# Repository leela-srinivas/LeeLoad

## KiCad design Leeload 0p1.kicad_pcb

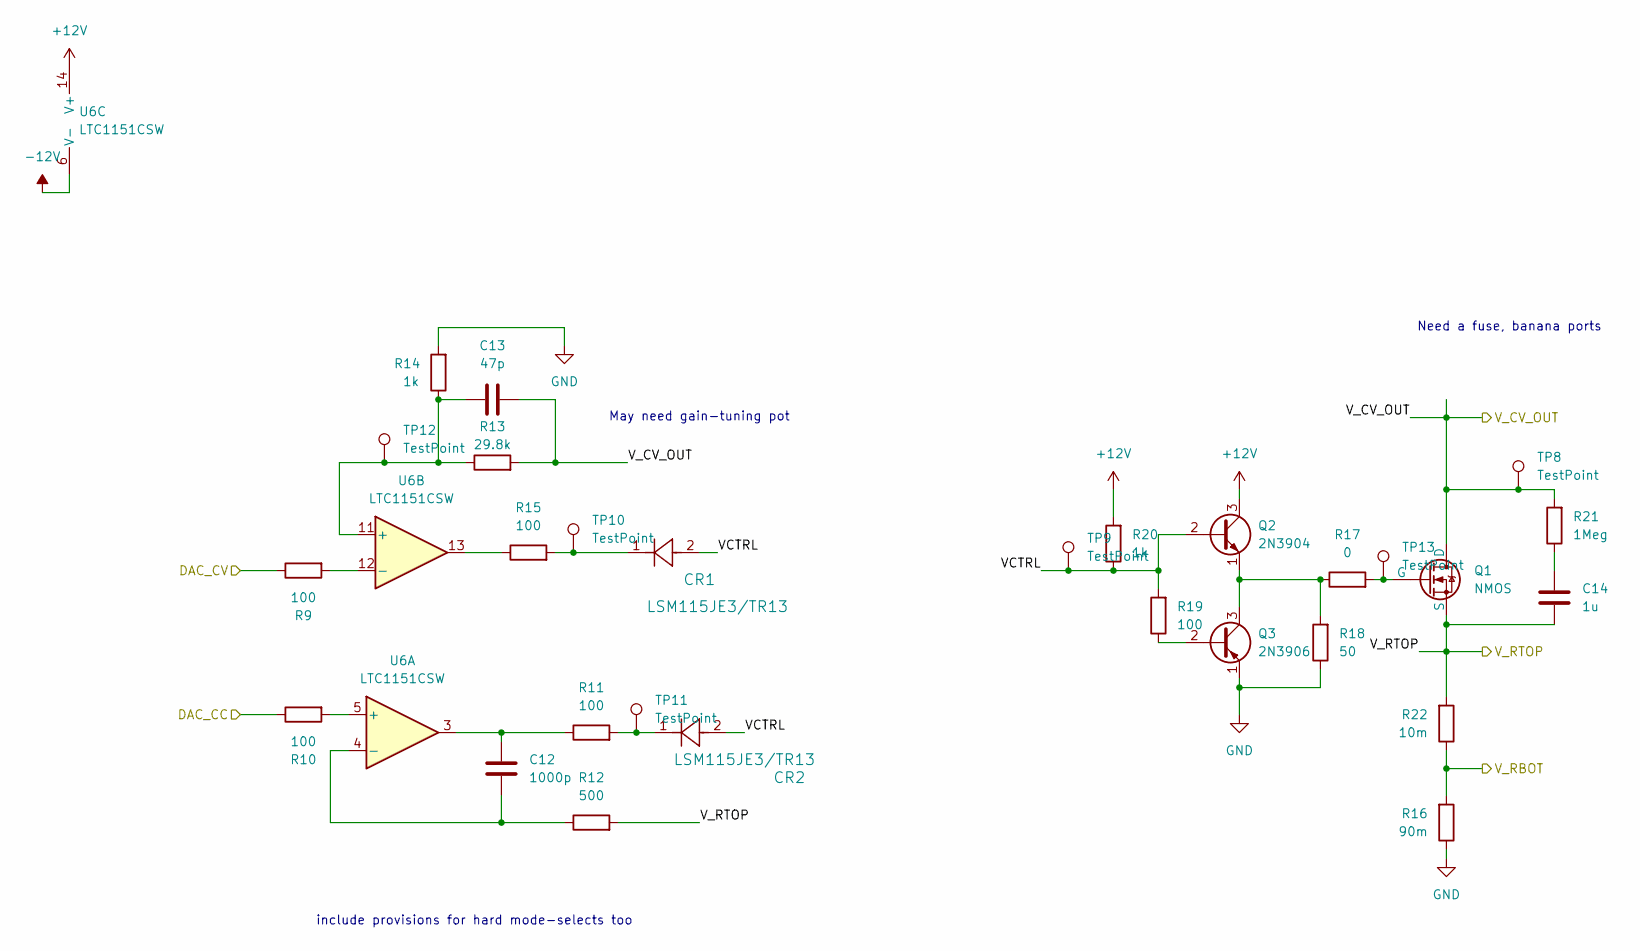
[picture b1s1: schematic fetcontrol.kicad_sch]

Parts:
C12: 1000p
C13: 47p; C_0402_1005Metric
C14: 1u; C_0402_1005Metric
CR1, CR2: LSM115JE3/TR13; DO-214BA_MCH
Q1: NMOS; TO-220-3_Vertical
Q2: 2N3904; TO-92_Inline
Q3: 2N3906; TO-92_Inline
R9, R10, R11, R15, R19: 100; R_0402_1005Metric
R12: 500; R_0402_1005Metric
R13: 29.8k; R_0402_1005Metric
R14, R20: 1k; R_0402_1005Metric
R16: 90m; R_Box_L26.0mm_W5.0mm_P20.00mm
R17: 0; R_0402_1005Metric
R18: 50; R_0402_1005Metric
R21: 1Meg; R_0402_1005Metric
R22: 10m; R_0402_1005Metric
TP8: TestPoint; TestPoint_Plated_Hole_D2.0mm
TP9, TP10, TP11, TP12, TP13: TestPoint; TestPoint_Pad_D1.0mm
U6: LTC1151CSW; SOIC-16W_7.5x10.3mm_P1.27mm

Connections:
12V_REG: Q2.3 (C), R20.2, U6.6 (V-), U6.14 (V+); also elsewhere on the board
/Arduino Control/DAC_CC: R10.1; also elsewhere on the board
/Arduino Control/DAC_CV: R9.1; also elsewhere on the board
/Arduino Control/IN-: R16.2, R22.1; also elsewhere on the board
/Control Loops, FET Control/VCTRL: CR1.2, CR2.2, Q2.2 (B), R19.2, R20.1, TP9.1
/Control Loops, FET Control/V_CV_OUT: C13.2, Q1.1 (D), R13.2, R21.2, TP8.1; also elsewhere on the board
/Control Loops, FET Control/V_RTOP: C14.1, Q1.3 (S), R12.2, R22.2; also elsewhere on the board
GND: Q3.1 (E), R14.2, R16.1, R18.1; also elsewhere on the board
unnamed: C12.1, R11.1, U6.3
unnamed: C14.2, R21.1
unnamed: CR1.1, R15.2, TP10.1
unnamed: CR2.1, R11.2, TP11.1
unnamed: Q1.2 (G), R17.2, TP13.1
unnamed: Q2.1 (E), Q3.3 (C), R17.1, R18.2
unnamed: Q3.2 (B), R19.1
unnamed: R15.1, U6.13
unnamed: R10.2, U6.5 (+)
unnamed: C12.2, R12.1, U6.4 (-)
unnamed: C13.1, R13.1, R14.1, TP12.1, U6.11 (+)
unnamed: R9.2, U6.12 (-)

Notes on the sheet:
include provisions for hard mode-selects too
Need a fuse, banana ports
May need gain-tuning pot

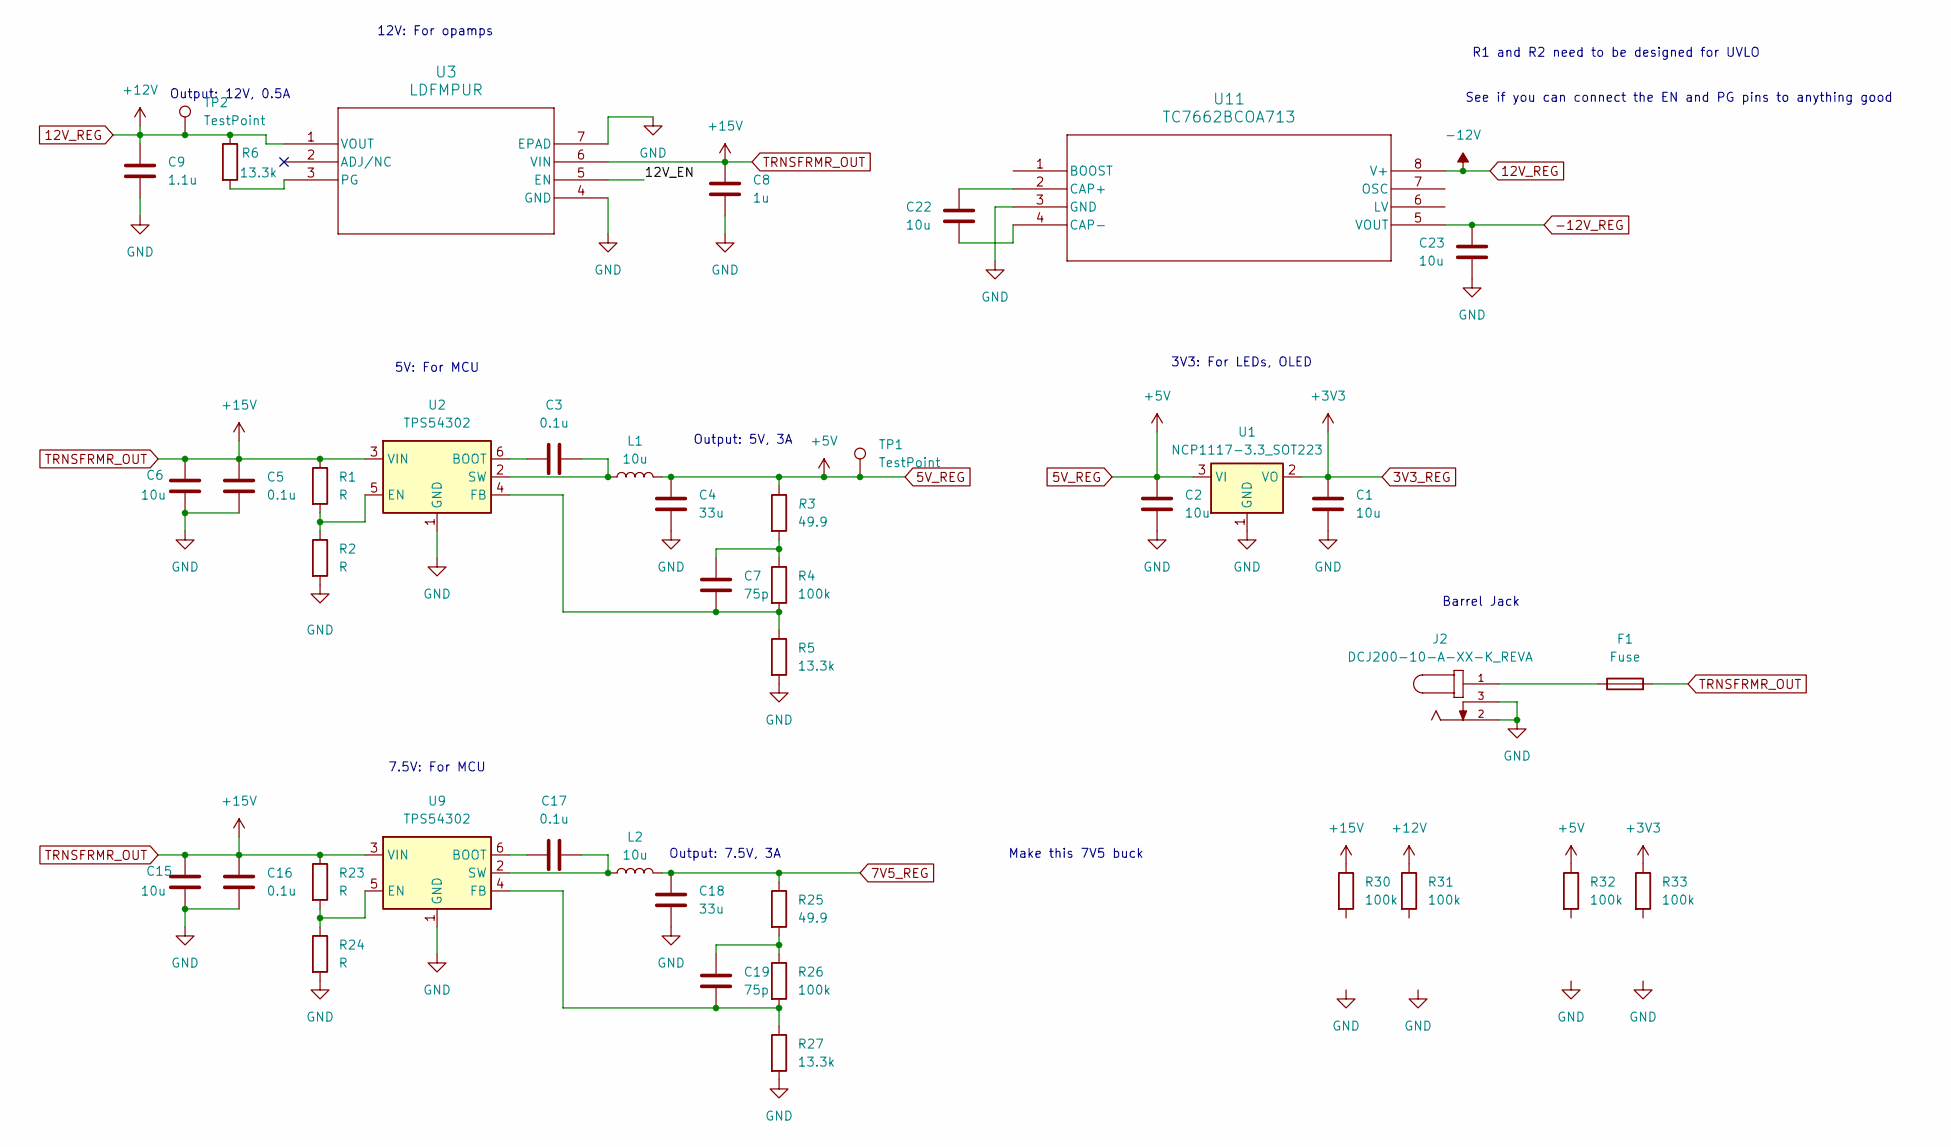
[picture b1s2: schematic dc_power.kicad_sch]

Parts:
C1, C2, C6: 10u; C_0603_1608Metric
C3: 0.1u; C_0805_2012Metric_Pad1.18x1.45mm_HandSolder
C4: 33u; C_0402_1005Metric
C5, C16, C17: 0.1u; C_0402_1005Metric
C7, C19: 75p; C_0402_1005Metric
C8: 1u; CP_Radial_D4.0mm_P2.00mm
C9: 1.1u; C_0805_2012Metric
C15: 10u; C_0402_1005Metric
C18: 33u; C_0805_2012Metric
C22, C23: 10u; CP_Radial_D5.0mm_P2.50mm
F1: Fuse
J2: DCJ200-10-A-XX-K_REVA; GCT_DCJ200-10-A-XX-K_REVA; PARTREV A
L1, L2: 10u; L_1206_3216Metric_Pad1.22x1.90mm_HandSolder
R1, R2: R; R_0402_1005Metric
R3: 49.9; R_0603_1608Metric
R4, R26: 100k; R_0603_1608Metric
R5, R27: 13.3k; R_0603_1608Metric
R6: 13.3k
R23, R24: R
R25: 49.9; C_0402_1005Metric
R30, R31, R32, R33: 100k
TP1, TP2: TestPoint; TestPoint_Plated_Hole_D2.0mm
U1: NCP1117-3.3_SOT223; SOT-223-3_TabPin2
U2, U9: TPS54302; SOT-23-6
U3: LDFMPUR; DFN6_3x3_LDFM_STM
U11: TC7662BCOA713; SOIC8-N_MC_MCH

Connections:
3V3_REG: C1.1, R33.1, U1.2 (VO); also elsewhere on the board
5V_REG: C2.1, C4.2, L1.2, R3.1, R32.1, TP1.1, U1.3 (VI); also elsewhere on the board
7V5_REG: C18.2, L2.2, R25.1
12V_REG: C9.2, R6.1, R31.1, TP2.1, U3.1 (VOUT), U11.8 (V+); also elsewhere on the board
-12V_REG: C23.1, U11.5 (VOUT)
/DC Power/12V_EN: U3.5 (EN)
GND: C1.2, C2.2, C4.1, C5.1, C6.2, C8.1, C9.1, C15.2, C16.1, C18.1, C23.2, J2.2, J2.3, R2.2, R5.2, R24.2, R27.2, U1.1 (GND), U2.1 (GND), U3.4 (GND), U3.7 (EPAD), U9.1 (GND), U11.3 (GND); also elsewhere on the board
unnamed: C7.2, R3.2, R4.1
unnamed: C19.2, R25.2, R26.1
unnamed: F1.1, J2.1
unnamed: C3.1, U2.6 (BOOT)
unnamed: R1.2, R2.1, U2.5 (EN)
unnamed: C7.1, R4.2, R5.1, U2.4 (FB)
unnamed: C3.2, L1.1, U2.2 (SW)
unnamed: R6.2, U3.3 (PG)
unnamed: C17.1, U9.6 (BOOT)
unnamed: R23.2, R24.1, U9.5 (EN)
unnamed: C19.1, R26.2, R27.1, U9.4 (FB)
unnamed: C17.2, L2.1, U9.2 (SW)
unnamed: C22.1, U11.2 (CAP+)
unnamed: C22.2, U11.4 (CAP-)
TRNSFRMR_OUT: C5.2, C6.1, C8.2, C15.1, C16.2, F1.2, R1.1, R23.1, R30.1, U2.3 (VIN), U3.6 (VIN), U9.3 (VIN)

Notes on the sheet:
R1 and R2 need to be designed for UVLO
See if you can connect the EN and PG pins to anything good
Output: 12V, 0.5A
5V: For MCU
Output: 7.5V, 3A
7.5V: For MCU
12V: For opamps
Output: 5V, 3A
3V3: For LEDs, OLED
Make this 7V5 buck
Barrel Jack

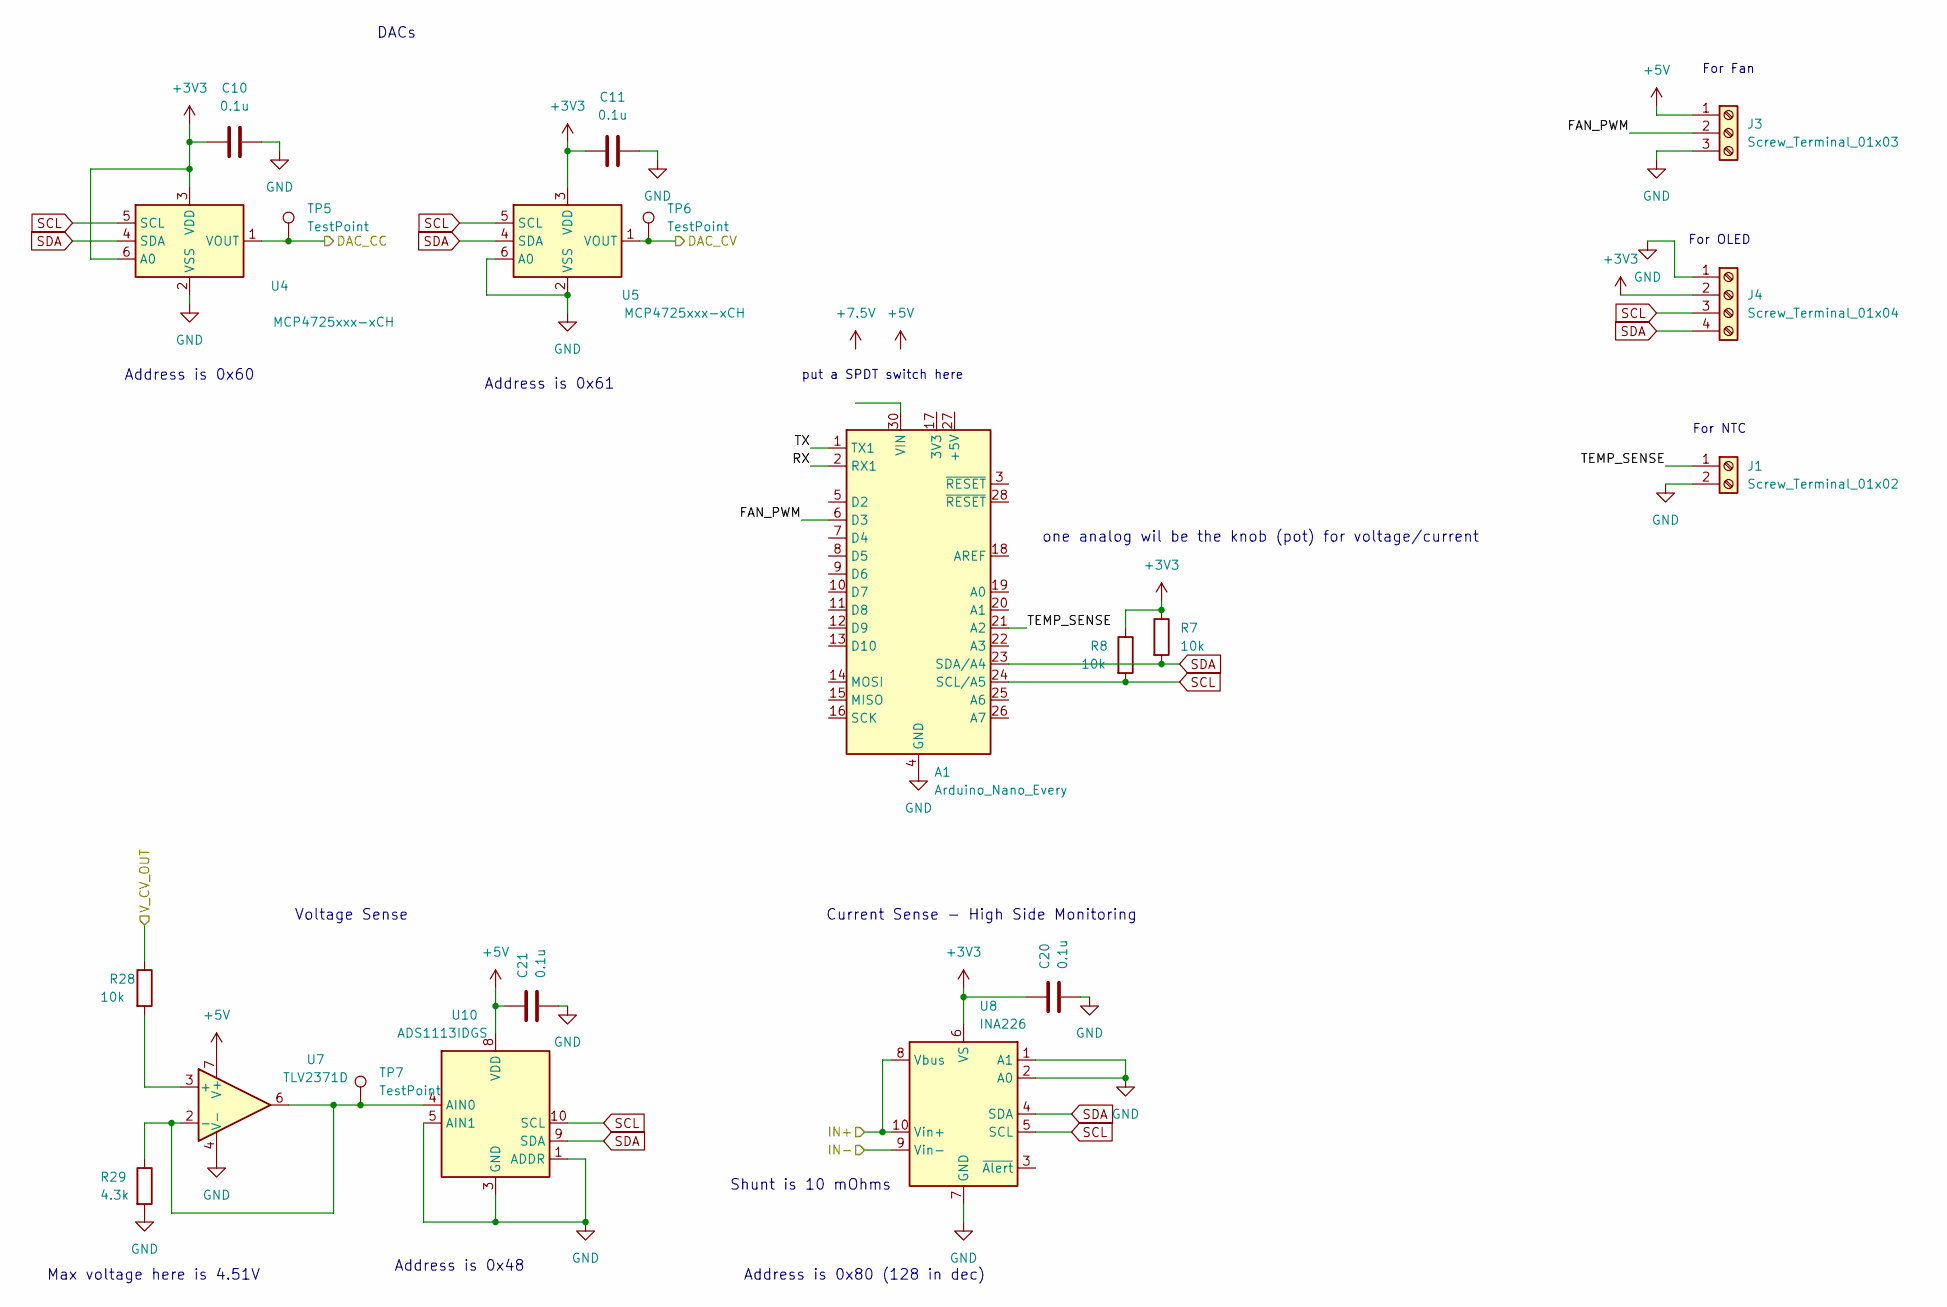
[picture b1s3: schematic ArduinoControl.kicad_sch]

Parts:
A1: Arduino_Nano_Every; Arduino_Nano
C10, C11, C20, C21: 0.1u; C_0402_1005Metric
J1: Screw_Terminal_01x02; TerminalBlock_WAGO_2601-3102_1x02_P3.50mm_Vertical
J3: Screw_Terminal_01x03; TerminalBlock_WAGO_2601-3103_1x03_P3.50mm_Vertical
J4: Screw_Terminal_01x04; TerminalBlock_WAGO_2601-3104_1x04_P3.50mm_Vertical
R7, R8: 10k; R_0402_1005Metric
R28: 10k; R_0603_1608Metric
R29: 4.3k; R_0603_1608Metric
TP5, TP6: TestPoint; TestPoint_Pad_D1.0mm
TP7: TestPoint; TestPoint_Plated_Hole_D2.0mm
U4, U5: MCP4725xxx-xCH; SOT-23-6
U7: TLV2371D; SOIC-8_3.9x4.9mm_P1.27mm
U8: INA226; VSSOP-10_3x3mm_P0.5mm
U10: ADS1113IDGS; TSSOP-10_3x3mm_P0.5mm

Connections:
3V3_REG: C10.1, C11.1, C20.2, J4.2, R7.1, R8.1, U4.3 (VDD), U4.6 (A0), U5.3 (VDD), U8.6 (VS); also elsewhere on the board
5V_REG: C21.2, J3.1, U7.7 (V+), U10.8 (VDD); also elsewhere on the board
/Arduino Control/DAC_CC: TP5.1, U4.1 (VOUT); also elsewhere on the board
/Arduino Control/DAC_CV: TP6.1, U5.1 (VOUT); also elsewhere on the board
/Arduino Control/FAN_PWM: A1.6 (D3), J3.2
/Arduino Control/IN-: U8.9 (Vin-); also elsewhere on the board
/Arduino Control/RX: A1.2 (RX1)
/Arduino Control/TEMP_SENSE: A1.21 (A2), J1.1
/Arduino Control/TX: A1.1 (TX1)
/Control Loops, FET Control/V_CV_OUT: R28.1; also elsewhere on the board
/Control Loops, FET Control/V_RTOP: U8.8 (Vbus), U8.10 (Vin+); also elsewhere on the board
GND: A1.4 (GND), A1.29 (GND), C10.2, C11.2, C20.1, C21.1, J1.2, J3.3, J4.1, R29.2, U4.2 (VSS), U5.2 (VSS), U5.6 (A0), U7.4 (V-), U8.1 (A1), U8.2 (A0), U8.7 (GND), U10.1 (ADDR), U10.3 (GND), U10.5 (AIN1); also elsewhere on the board
unnamed: R28.2, U7.3 (+)
unnamed: R29.1, TP7.1, U7.2 (-), U7.6, U10.4 (AIN0)
SCL: A1.24 (SCL/A5), J4.3, R8.2, U4.5 (SCL), U5.5 (SCL), U8.5 (SCL), U10.10 (SCL)
SDA: A1.23 (SDA/A4), J4.4, R7.2, U4.4 (SDA), U5.4 (SDA), U8.4 (SDA), U10.9 (SDA)

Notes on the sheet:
For NTC
Voltage Sense
For OLED
Address is 0x61
Address is 0x48
Max voltage here is 4.51V
one analog wil be the knob (pot) for voltage/current
Current Sense - High Side Monitoring
put a SPDT switch here
Shunt is 10 mOhms
For Fan
Address is 0x80 (128 in dec)
DACs
Address is 0x60

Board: 2 copper layers, 82 parts (0 on the bottom side), 42 nets, no tracks yet.
